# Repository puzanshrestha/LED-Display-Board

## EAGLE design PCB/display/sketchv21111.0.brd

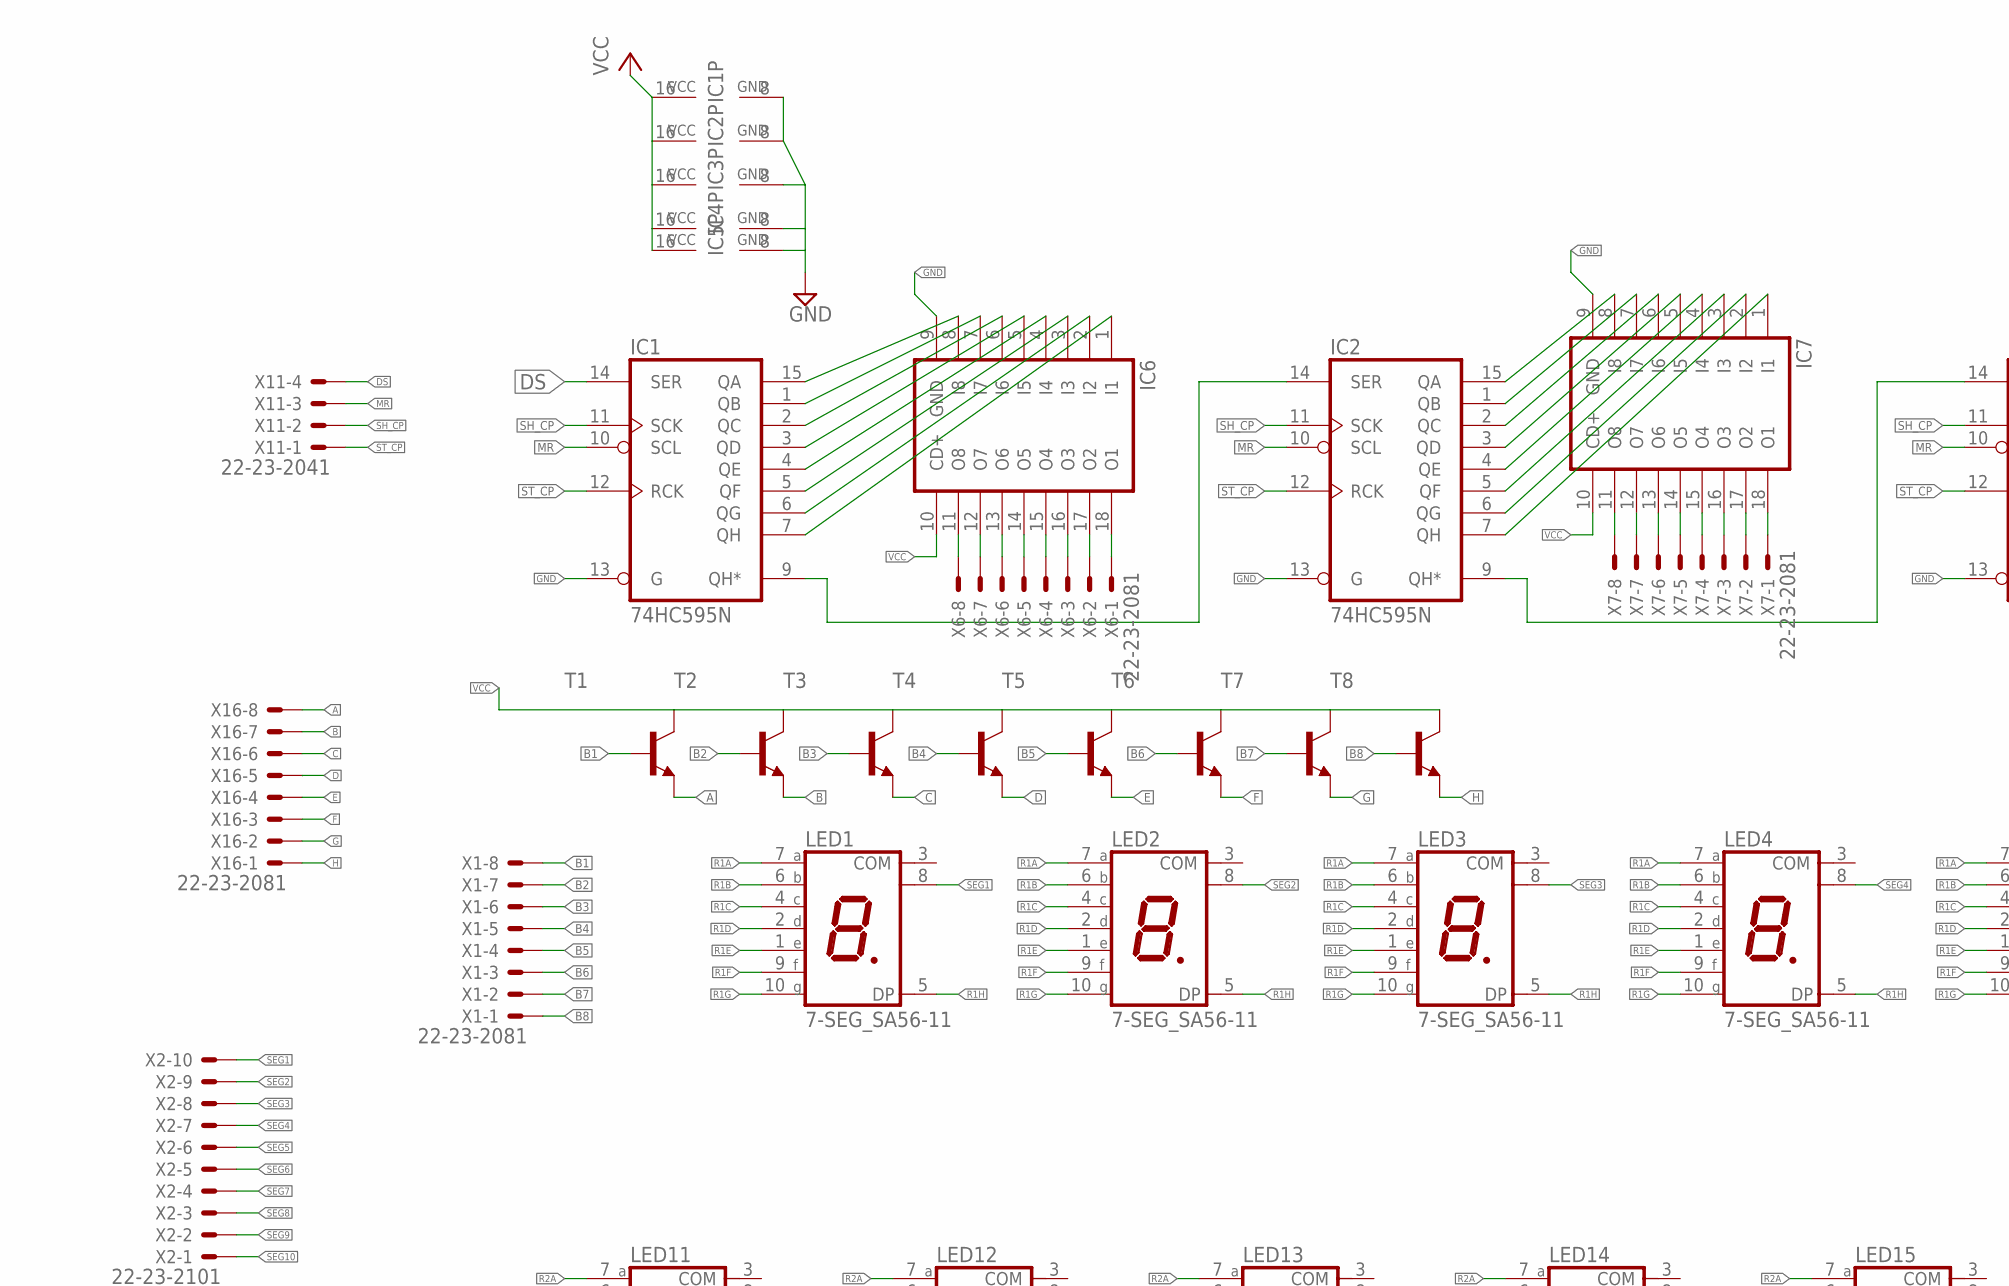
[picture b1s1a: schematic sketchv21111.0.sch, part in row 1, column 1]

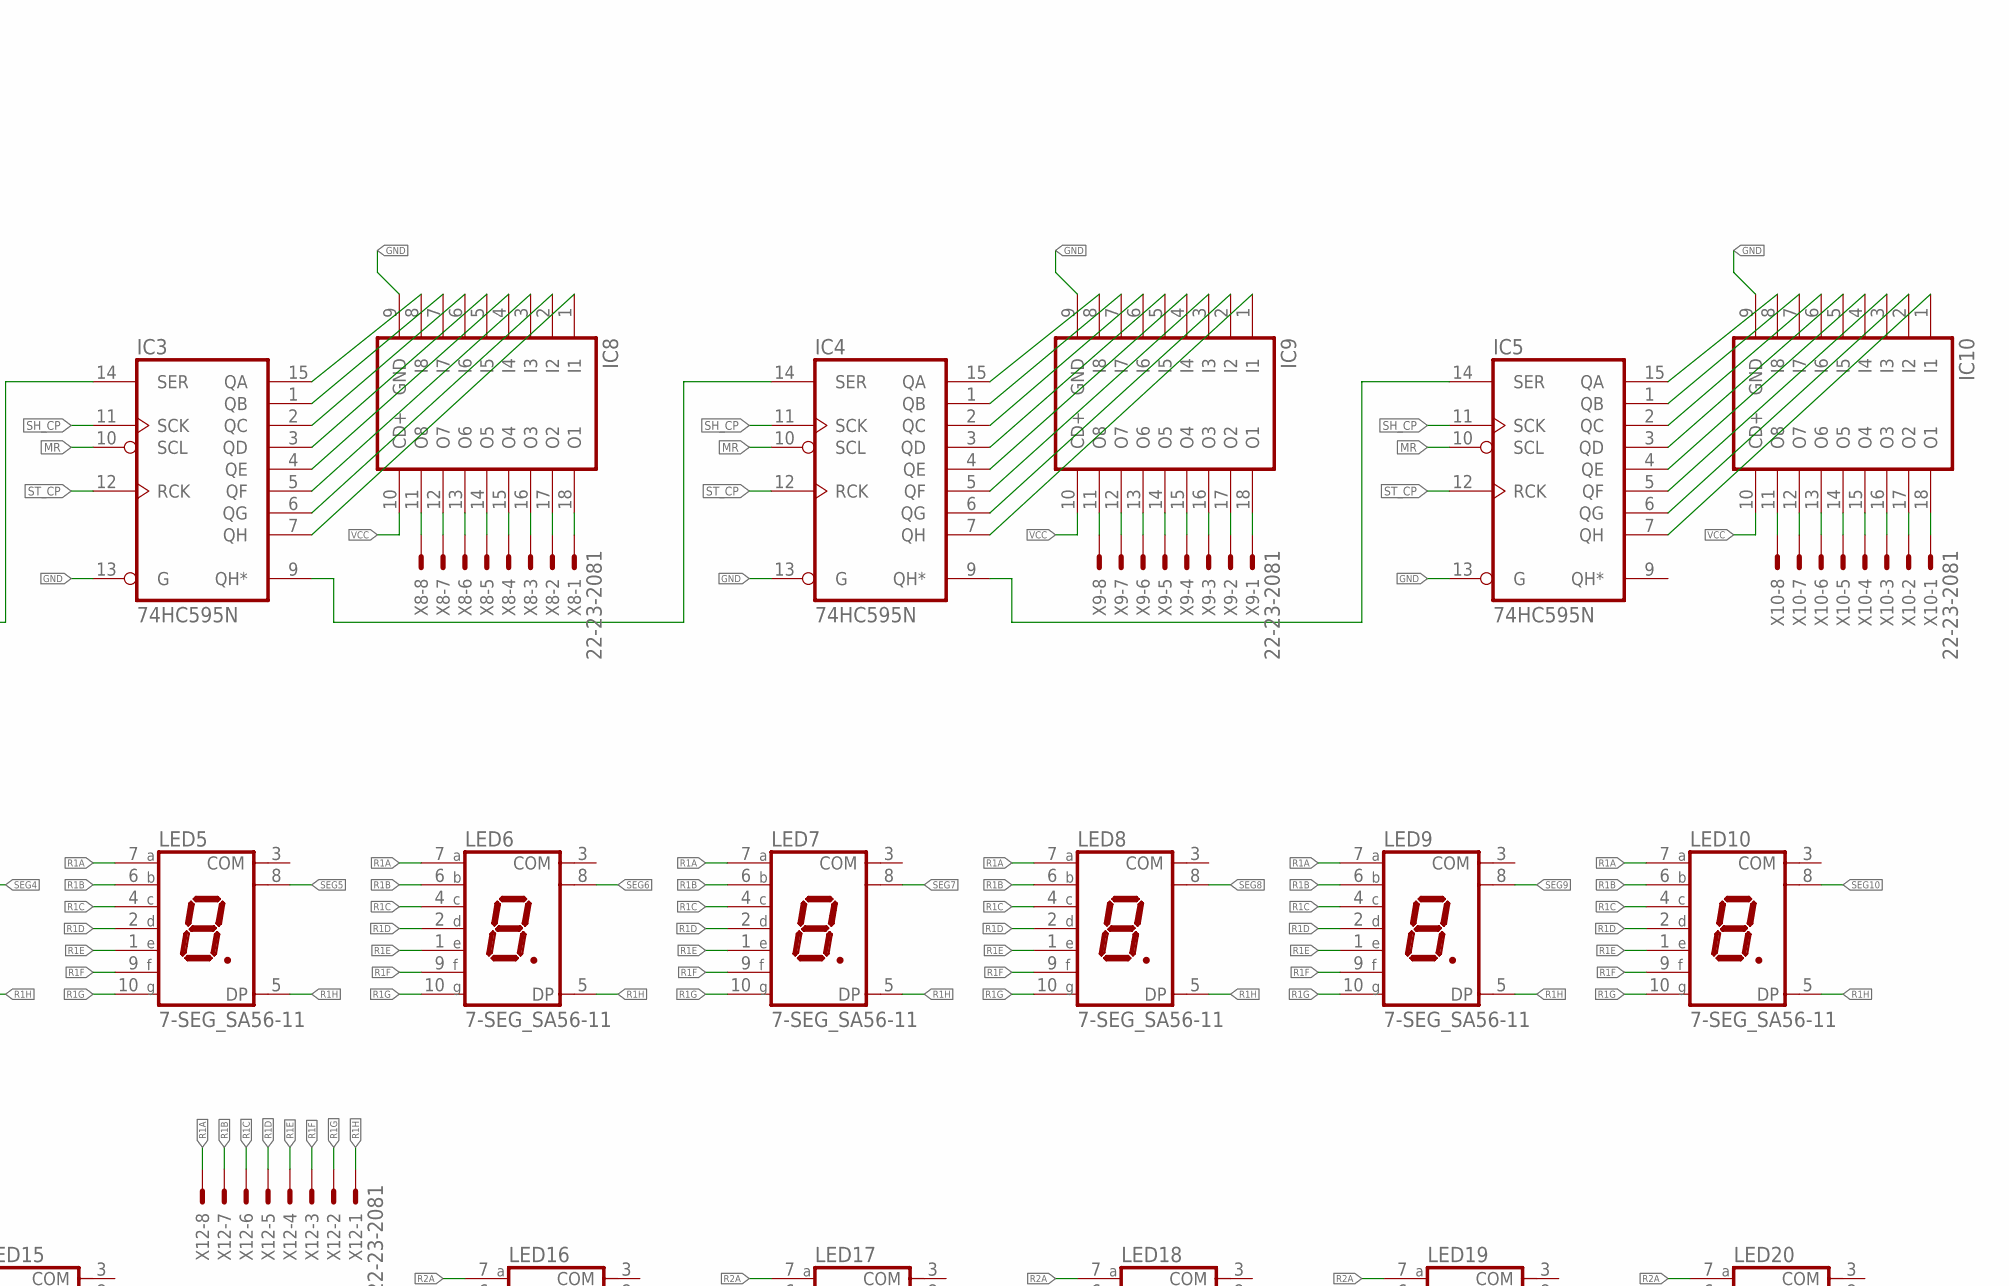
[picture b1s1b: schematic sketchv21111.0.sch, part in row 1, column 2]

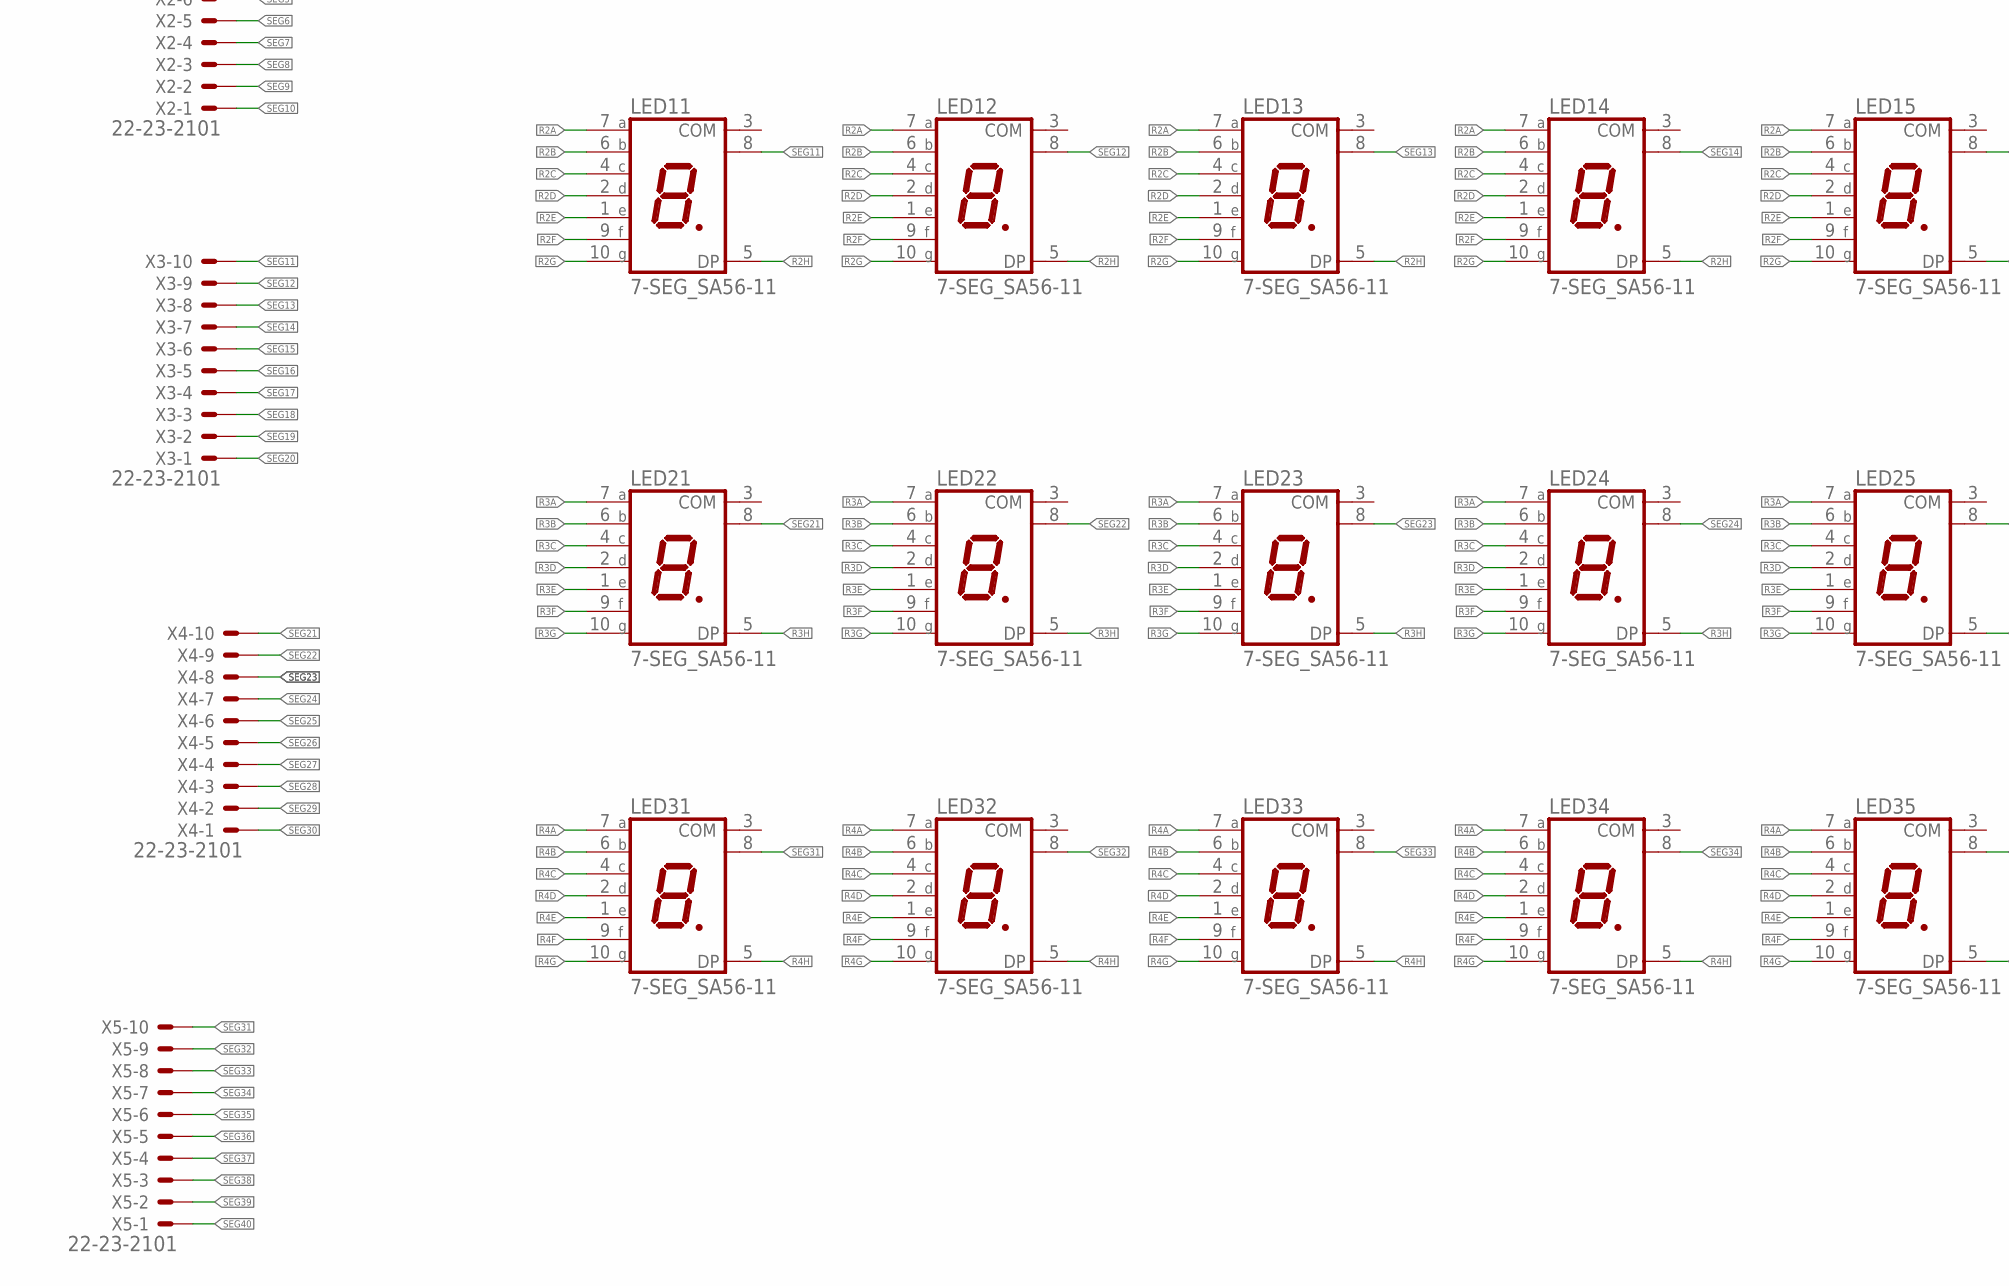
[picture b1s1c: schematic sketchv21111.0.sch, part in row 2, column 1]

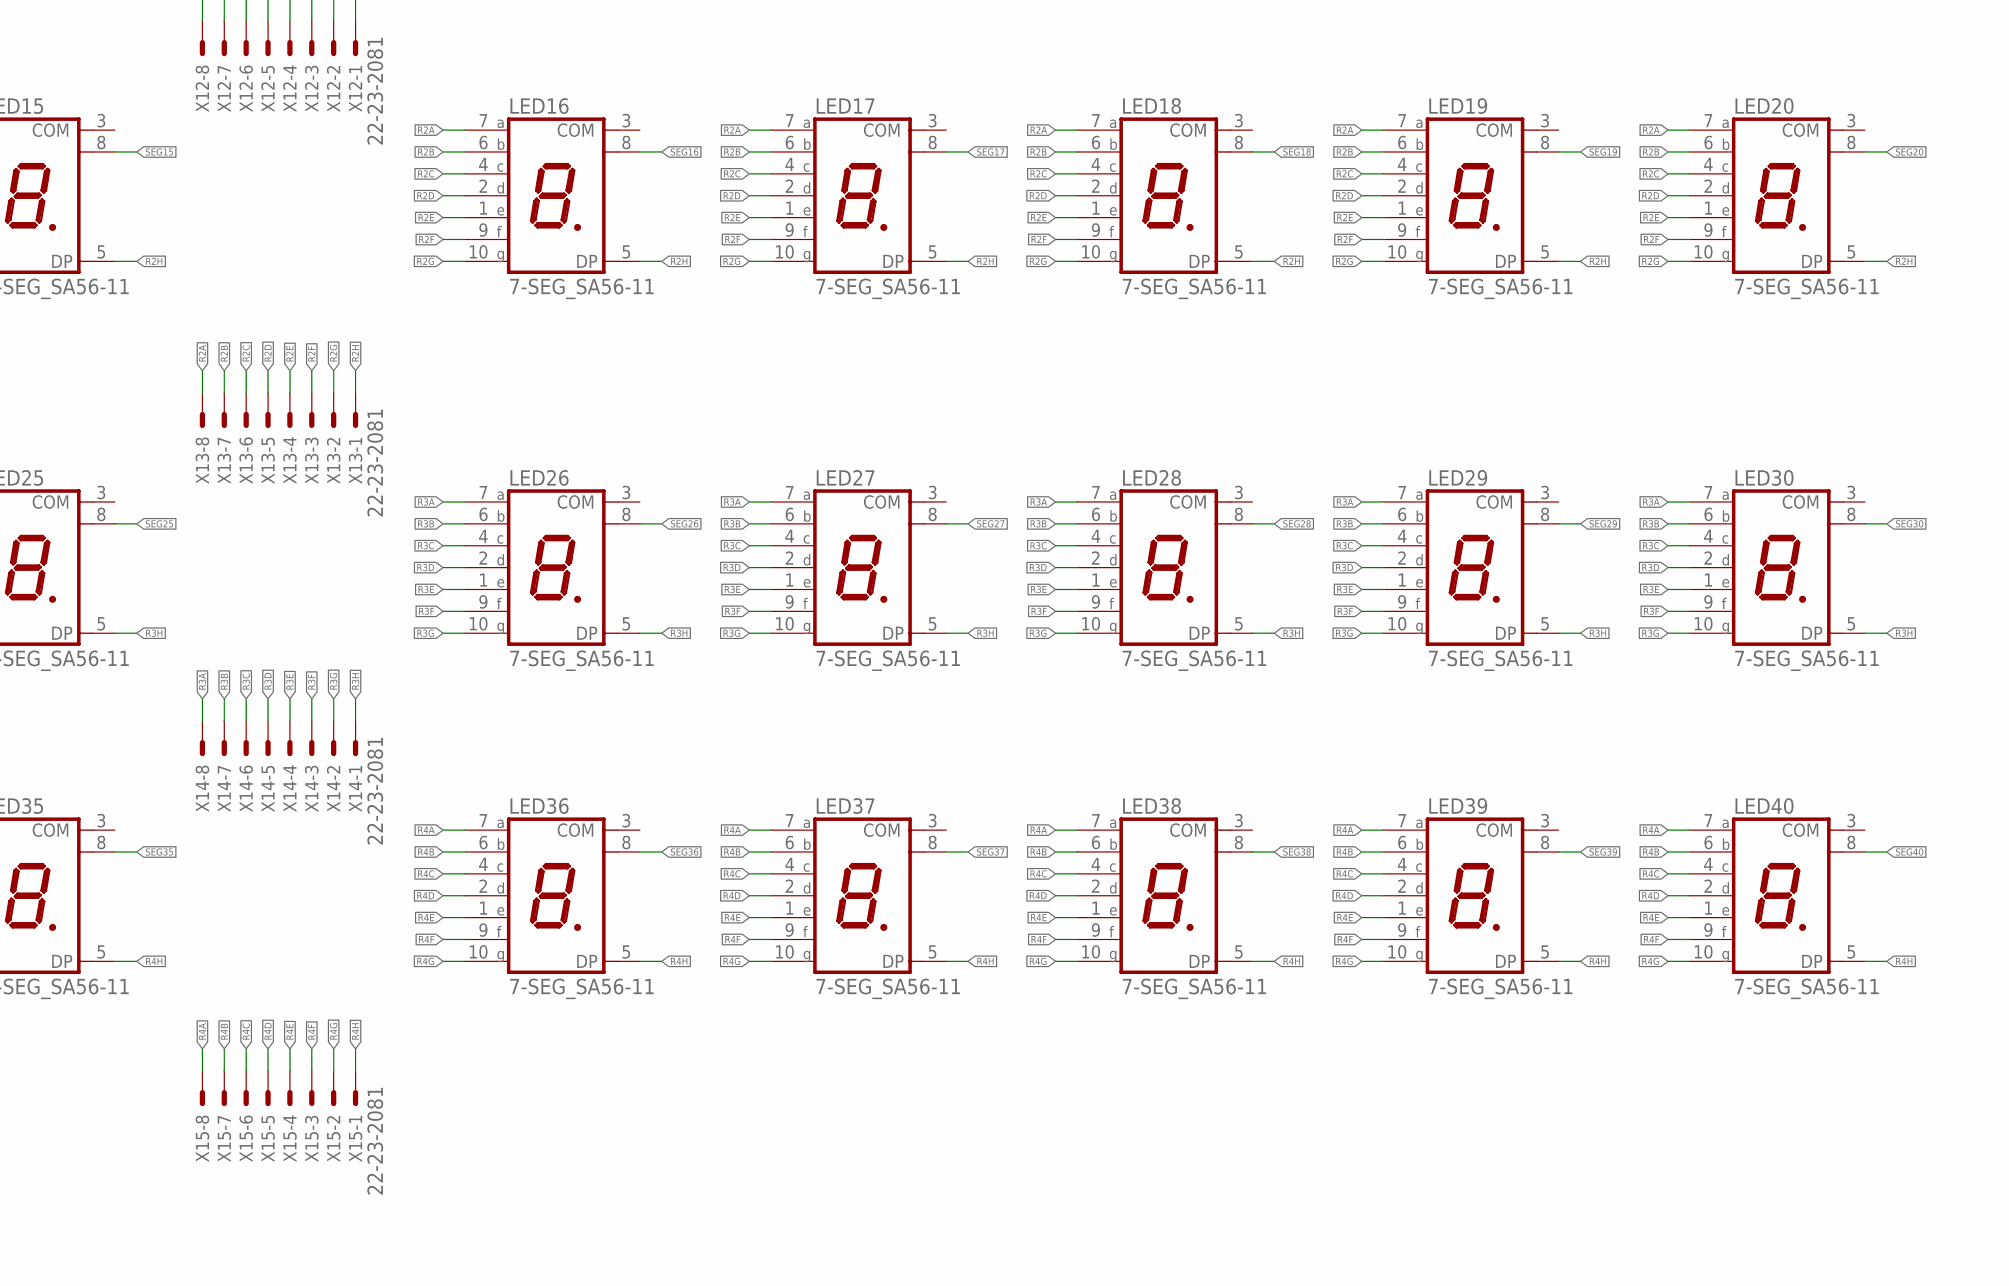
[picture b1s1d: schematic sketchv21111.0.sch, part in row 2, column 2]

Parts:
IC1, IC2, IC3, IC4, IC5: 74HC595N; DIL16
IC6, IC7, IC8, IC9, IC10: ULN2803A; DIL18
LED1, LED2, LED3, LED4, LED5, LED6, LED7, LED8, LED9, LED10, LED11, LED12, LED13, LED14, LED15, LED16, LED17, LED18, LED19, LED20, LED21, LED22, LED23, LED24, LED25, LED26, LED27, LED28, LED29, LED30, LED31, LED32, LED33, LED34, LED35, LED36, LED37, LED38, LED39, LED40: 7-SEG_SA56-11; SA56-11
T1, T2, T3, T4, T5, T6, T7, T8: -NPN-TO92; TO92
X1, X6, X7, X8, X9, X10, X12, X13, X14, X15, X16: 22-23-2081
X2, X3, X4, X5: 22-23-2101
X11: 22-23-2041

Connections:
A: T1.1 (E), X16.8
B: T2.1 (E), X16.7
B1: T1.2 (B), X1.8
B2: T2.2 (B), X1.7
B3: T3.2 (B), X1.6
B4: T4.2 (B), X1.5
B5: T5.2 (B), X1.4
B6: T6.2 (B), X1.3
B7: T7.2 (B), X1.2
B8: T8.2 (B), X1.1
C: T3.1 (E), X16.6
D: T4.1 (E), X16.5
DS: IC1.14 (SER), X11.4
E: T5.1 (E), X16.4
F: T6.1 (E), X16.3
G: T7.1 (E), X16.2
GND: IC1.8 (GND), IC1.13 (G), IC2.8 (GND), IC2.13 (G), IC3.8 (GND), IC3.13 (G), IC4.8 (GND), IC4.13 (G), IC5.8 (GND), IC5.13 (G), IC6.9 (GND), IC7.9 (GND), IC8.9 (GND), IC9.9 (GND), IC10.9 (GND)
H: T8.1 (E), X16.1
MR: IC1.10 (SCL), IC2.10 (SCL), IC3.10 (SCL), IC4.10 (SCL), IC5.10 (SCL), X11.3
unnamed: IC1.15 (QA), IC6.8 (I8)
unnamed: IC1.1 (QB), IC6.7 (I7)
unnamed: IC1.2 (QC), IC6.6 (I6)
unnamed: IC1.3 (QD), IC6.5 (I5)
unnamed: IC1.4 (QE), IC6.4 (I4)
unnamed: IC1.5 (QF), IC6.3 (I3)
unnamed: IC1.6 (QG), IC6.2 (I2)
unnamed: IC1.7 (QH), IC6.1 (I1)
unnamed: IC2.15 (QA), IC7.8 (I8)
unnamed: IC2.1 (QB), IC7.7 (I7)
unnamed: IC2.2 (QC), IC7.6 (I6)
unnamed: IC2.3 (QD), IC7.5 (I5)
unnamed: IC2.4 (QE), IC7.4 (I4)
unnamed: IC2.5 (QF), IC7.3 (I3)
unnamed: IC2.6 (QG), IC7.2 (I2)
unnamed: IC2.7 (QH), IC7.1 (I1)
unnamed: IC3.15 (QA), IC8.8 (I8)
unnamed: IC3.1 (QB), IC8.7 (I7)
unnamed: IC3.2 (QC), IC8.6 (I6)
unnamed: IC3.3 (QD), IC8.5 (I5)
unnamed: IC3.4 (QE), IC8.4 (I4)
unnamed: IC3.5 (QF), IC8.3 (I3)
unnamed: IC3.6 (QG), IC8.2 (I2)
unnamed: IC3.7 (QH), IC8.1 (I1)
unnamed: IC4.15 (QA), IC9.8 (I8)
unnamed: IC4.1 (QB), IC9.7 (I7)
unnamed: IC4.2 (QC), IC9.6 (I6)
unnamed: IC4.3 (QD), IC9.5 (I5)
unnamed: IC4.4 (QE), IC9.4 (I4)
unnamed: IC4.5 (QF), IC9.3 (I3)
unnamed: IC4.6 (QG), IC9.2 (I2)
unnamed: IC4.7 (QH), IC9.1 (I1)
unnamed: IC5.15 (QA), IC10.8 (I8)
unnamed: IC5.1 (QB), IC10.7 (I7)
unnamed: IC5.2 (QC), IC10.6 (I6)
unnamed: IC5.3 (QD), IC10.5 (I5)
unnamed: IC5.4 (QE), IC10.4 (I4)
unnamed: IC5.5 (QF), IC10.3 (I3)
unnamed: IC5.6 (QG), IC10.2 (I2)
unnamed: IC5.7 (QH), IC10.1 (I1)
unnamed: IC1.9 (QH*), IC2.14 (SER)
unnamed: IC6.11 (O8), X6.8
unnamed: IC6.12 (O7), X6.7
unnamed: IC6.13 (O6), X6.6
unnamed: IC6.14 (O5), X6.5
unnamed: IC6.15 (O4), X6.4
unnamed: IC6.16 (O3), X6.3
unnamed: IC6.17 (O2), X6.2
unnamed: IC6.18 (O1), X6.1
unnamed: IC7.11 (O8), X7.8
unnamed: IC7.12 (O7), X7.7
unnamed: IC7.13 (O6), X7.6
unnamed: IC7.14 (O5), X7.5
unnamed: IC7.15 (O4), X7.4
unnamed: IC7.16 (O3), X7.3
unnamed: IC7.17 (O2), X7.2
unnamed: IC7.18 (O1), X7.1
unnamed: IC8.11 (O8), X8.8
unnamed: IC8.12 (O7), X8.7
unnamed: IC8.13 (O6), X8.6
unnamed: IC8.14 (O5), X8.5
unnamed: IC8.15 (O4), X8.4
unnamed: IC8.16 (O3), X8.3
unnamed: IC8.17 (O2), X8.2
unnamed: IC8.18 (O1), X8.1
unnamed: IC9.11 (O8), X9.8
unnamed: IC9.12 (O7), X9.7
unnamed: IC9.13 (O6), X9.6
unnamed: IC9.14 (O5), X9.5
unnamed: IC9.15 (O4), X9.4
unnamed: IC9.16 (O3), X9.3
unnamed: IC9.17 (O2), X9.2
unnamed: IC9.18 (O1), X9.1
unnamed: IC10.11 (O8), X10.8
unnamed: IC10.12 (O7), X10.7
unnamed: IC10.13 (O6), X10.6
unnamed: IC10.14 (O5), X10.5
unnamed: IC10.15 (O4), X10.4
unnamed: IC10.16 (O3), X10.3
unnamed: IC10.17 (O2), X10.2
unnamed: IC10.18 (O1), X10.1
unnamed: IC2.9 (QH*), IC3.14 (SER)
unnamed: IC3.9 (QH*), IC4.14 (SER)
unnamed: IC4.9 (QH*), IC5.14 (SER)
R1A: LED1.7 (A), LED2.7 (A), LED3.7 (A), LED4.7 (A), LED5.7 (A), LED6.7 (A), LED7.7 (A), LED8.7 (A), LED9.7 (A), LED10.7 (A), X12.8
R1B: LED1.6 (B), LED2.6 (B), LED3.6 (B), LED4.6 (B), LED5.6 (B), LED6.6 (B), LED7.6 (B), LED8.6 (B), LED9.6 (B), LED10.6 (B), X12.7
R1C: LED1.4 (C), LED2.4 (C), LED3.4 (C), LED4.4 (C), LED5.4 (C), LED6.4 (C), LED7.4 (C), LED8.4 (C), LED9.4 (C), LED10.4 (C), X12.6
R1D: LED1.2 (D), LED2.2 (D), LED3.2 (D), LED4.2 (D), LED5.2 (D), LED6.2 (D), LED7.2 (D), LED8.2 (D), LED9.2 (D), LED10.2 (D), X12.5
R1E: LED1.1 (E), LED2.1 (E), LED3.1 (E), LED4.1 (E), LED5.1 (E), LED6.1 (E), LED7.1 (E), LED8.1 (E), LED9.1 (E), LED10.1 (E), X12.4
R1F: LED1.9 (F), LED2.9 (F), LED3.9 (F), LED4.9 (F), LED5.9 (F), LED6.9 (F), LED7.9 (F), LED8.9 (F), LED9.9 (F), LED10.9 (F), X12.3
R1G: LED1.10 (G), LED2.10 (G), LED3.10 (G), LED4.10 (G), LED5.10 (G), LED6.10 (G), LED7.10 (G), LED8.10 (G), LED9.10 (G), LED10.10 (G), X12.2
R1H: LED1.5 (DP), LED2.5 (DP), LED3.5 (DP), LED4.5 (DP), LED5.5 (DP), LED6.5 (DP), LED7.5 (DP), LED8.5 (DP), LED9.5 (DP), LED10.5 (DP), X12.1
R2A: LED11.7 (A), LED12.7 (A), LED13.7 (A), LED14.7 (A), LED15.7 (A), LED16.7 (A), LED17.7 (A), LED18.7 (A), LED19.7 (A), LED20.7 (A), X13.8
R2B: LED11.6 (B), LED12.6 (B), LED13.6 (B), LED14.6 (B), LED15.6 (B), LED16.6 (B), LED17.6 (B), LED18.6 (B), LED19.6 (B), LED20.6 (B), X13.7
R2C: LED11.4 (C), LED12.4 (C), LED13.4 (C), LED14.4 (C), LED15.4 (C), LED16.4 (C), LED17.4 (C), LED18.4 (C), LED19.4 (C), LED20.4 (C), X13.6
R2D: LED11.2 (D), LED12.2 (D), LED13.2 (D), LED14.2 (D), LED15.2 (D), LED16.2 (D), LED17.2 (D), LED18.2 (D), LED19.2 (D), LED20.2 (D), X13.5
R2E: LED11.1 (E), LED12.1 (E), LED13.1 (E), LED14.1 (E), LED15.1 (E), LED16.1 (E), LED17.1 (E), LED18.1 (E), LED19.1 (E), LED20.1 (E), X13.4
R2F: LED11.9 (F), LED12.9 (F), LED13.9 (F), LED14.9 (F), LED15.9 (F), LED16.9 (F), LED17.9 (F), LED18.9 (F), LED19.9 (F), LED20.9 (F), X13.3
R2G: LED11.10 (G), LED12.10 (G), LED13.10 (G), LED14.10 (G), LED15.10 (G), LED16.10 (G), LED17.10 (G), LED18.10 (G), LED19.10 (G), LED20.10 (G), X13.2
R2H: LED11.5 (DP), LED12.5 (DP), LED13.5 (DP), LED14.5 (DP), LED15.5 (DP), LED16.5 (DP), LED17.5 (DP), LED18.5 (DP), LED19.5 (DP), LED20.5 (DP), X13.1
R3A: LED21.7 (A), LED22.7 (A), LED23.7 (A), LED24.7 (A), LED25.7 (A), LED26.7 (A), LED27.7 (A), LED28.7 (A), LED29.7 (A), LED30.7 (A), X14.8
R3B: LED21.6 (B), LED22.6 (B), LED23.6 (B), LED24.6 (B), LED25.6 (B), LED26.6 (B), LED27.6 (B), LED28.6 (B), LED29.6 (B), LED30.6 (B), X14.7
R3C: LED21.4 (C), LED22.4 (C), LED23.4 (C), LED24.4 (C), LED25.4 (C), LED26.4 (C), LED27.4 (C), LED28.4 (C), LED29.4 (C), LED30.4 (C), X14.6
R3D: LED21.2 (D), LED22.2 (D), LED23.2 (D), LED24.2 (D), LED25.2 (D), LED26.2 (D), LED27.2 (D), LED28.2 (D), LED29.2 (D), LED30.2 (D), X14.5
R3E: LED21.1 (E), LED22.1 (E), LED23.1 (E), LED24.1 (E), LED25.1 (E), LED26.1 (E), LED27.1 (E), LED28.1 (E), LED29.1 (E), LED30.1 (E), X14.4
R3F: LED21.9 (F), LED22.9 (F), LED23.9 (F), LED24.9 (F), LED25.9 (F), LED26.9 (F), LED27.9 (F), LED28.9 (F), LED29.9 (F), LED30.9 (F), X14.3
R3G: LED21.10 (G), LED22.10 (G), LED23.10 (G), LED24.10 (G), LED25.10 (G), LED26.10 (G), LED27.10 (G), LED28.10 (G), LED29.10 (G), LED30.10 (G), X14.2
R3H: LED21.5 (DP), LED22.5 (DP), LED23.5 (DP), LED24.5 (DP), LED25.5 (DP), LED26.5 (DP), LED27.5 (DP), LED28.5 (DP), LED29.5 (DP), LED30.5 (DP), X14.1
R4A: LED31.7 (A), LED32.7 (A), LED33.7 (A), LED34.7 (A), LED35.7 (A), LED36.7 (A), LED37.7 (A), LED38.7 (A), LED39.7 (A), LED40.7 (A), X15.8
R4B: LED31.6 (B), LED32.6 (B), LED33.6 (B), LED34.6 (B), LED35.6 (B), LED36.6 (B), LED37.6 (B), LED38.6 (B), LED39.6 (B), LED40.6 (B), X15.7
R4C: LED31.4 (C), LED32.4 (C), LED33.4 (C), LED34.4 (C), LED35.4 (C), LED36.4 (C), LED37.4 (C), LED38.4 (C), LED39.4 (C), LED40.4 (C), X15.6
R4D: LED31.2 (D), LED32.2 (D), LED33.2 (D), LED34.2 (D), LED35.2 (D), LED36.2 (D), LED37.2 (D), LED38.2 (D), LED39.2 (D), LED40.2 (D), X15.5
R4E: LED31.1 (E), LED32.1 (E), LED33.1 (E), LED34.1 (E), LED35.1 (E), LED36.1 (E), LED37.1 (E), LED38.1 (E), LED39.1 (E), LED40.1 (E), X15.4
R4F: LED31.9 (F), LED32.9 (F), LED33.9 (F), LED34.9 (F), LED35.9 (F), LED36.9 (F), LED37.9 (F), LED38.9 (F), LED39.9 (F), LED40.9 (F), X15.3
R4G: LED31.10 (G), LED32.10 (G), LED33.10 (G), LED34.10 (G), LED35.10 (G), LED36.10 (G), LED37.10 (G), LED38.10 (G), LED39.10 (G), LED40.10 (G), X15.2
R4H: LED31.5 (DP), LED32.5 (DP), LED33.5 (DP), LED34.5 (DP), LED35.5 (DP), LED36.5 (DP), LED37.5 (DP), LED38.5 (DP), LED39.5 (DP), LED40.5 (DP), X15.1
SEG1: LED1.8 (COM), X2.10
SEG2: LED2.8 (COM), X2.9
SEG3: LED3.8 (COM), X2.8
SEG4: LED4.8 (COM), X2.7
SEG5: LED5.8 (COM), X2.6
SEG6: LED6.8 (COM), X2.5
SEG7: LED7.8 (COM), X2.4
SEG8: LED8.8 (COM), X2.3
SEG9: LED9.8 (COM), X2.2
SEG10: LED10.8 (COM), X2.1
SEG11: LED11.8 (COM), X3.10
SEG12: LED12.8 (COM), X3.9
SEG13: LED13.8 (COM), X3.8
SEG14: LED14.8 (COM), X3.7
SEG15: LED15.8 (COM), X3.6
SEG16: LED16.8 (COM), X3.5
SEG17: LED17.8 (COM), X3.4
SEG18: LED18.8 (COM), X3.3
SEG19: LED19.8 (COM), X3.2
SEG20: LED20.8 (COM), X3.1
SEG21: LED21.8 (COM), X4.10
SEG22: LED22.8 (COM), X4.9
SEG23: LED23.8 (COM), X4.8
SEG24: LED24.8 (COM), X4.7
SEG25: LED25.8 (COM), X4.6
SEG26: LED26.8 (COM), X4.5
SEG27: LED27.8 (COM), X4.4
SEG28: LED28.8 (COM), X4.3
SEG29: LED29.8 (COM), X4.2
SEG30: LED30.8 (COM), X4.1
SEG31: LED31.8 (COM), X5.10
SEG32: LED32.8 (COM), X5.9
SEG33: LED33.8 (COM), X5.8
SEG34: LED34.8 (COM), X5.7
SEG35: LED35.8 (COM), X5.6
SEG36: LED36.8 (COM), X5.5
SEG37: LED37.8 (COM), X5.4
SEG38: LED38.8 (COM), X5.3
SEG39: LED39.8 (COM), X5.2
SEG40: LED40.8 (COM), X5.1
SH_CP: IC1.11 (SCK), IC2.11 (SCK), IC3.11 (SCK), IC4.11 (SCK), IC5.11 (SCK), X11.2
ST_CP: IC1.12 (RCK), IC2.12 (RCK), IC3.12 (RCK), IC4.12 (RCK), IC5.12 (RCK), X11.1
VCC: IC1.16 (VCC), IC2.16 (VCC), IC3.16 (VCC), IC4.16 (VCC), IC5.16 (VCC), IC6.10 (CD+), IC7.10 (CD+), IC8.10 (CD+), IC9.10 (CD+), IC10.10 (CD+), T1.3 (C), T2.3 (C), T3.3 (C), T4.3 (C), T5.3 (C), T6.3 (C), T7.3 (C), T8.3 (C)

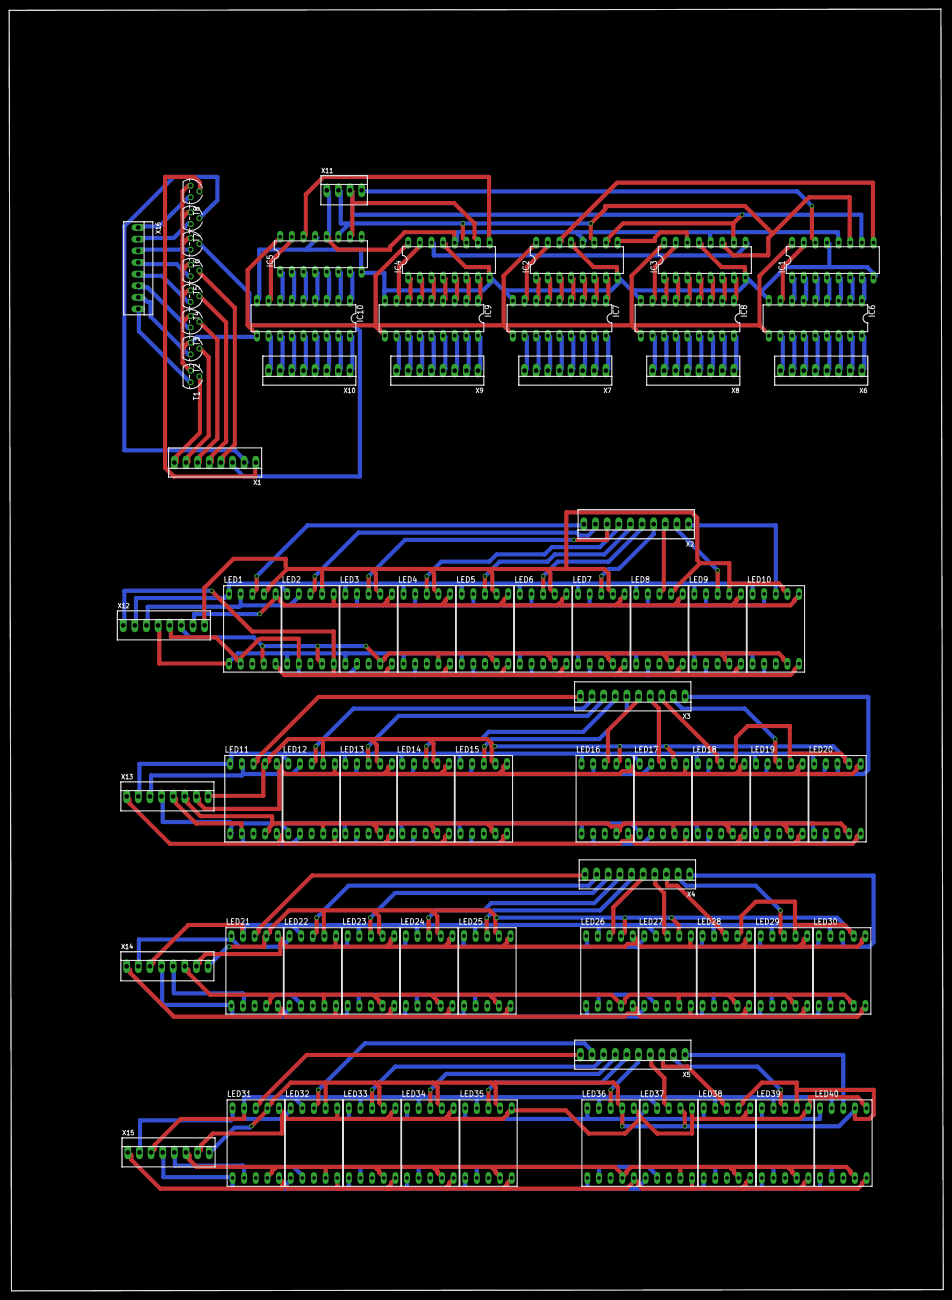
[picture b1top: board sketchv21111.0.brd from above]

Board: 2 copper layers, 203.9 x 279.8 mm, 74 parts (0 on the bottom side), 178 nets.
